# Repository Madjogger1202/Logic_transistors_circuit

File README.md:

# Logic_transistors_circuit

**Демонстрационная плата логических вентилей OR, AND и NOT на дискретных транзисторах с питанием от USB.**

Наглядная плата, на которой базовые логические вентили — **OR**, **AND** и **NOT** — собраны на дискретных транзисторах. Питание от USB, входы и выходы выведены на контактные площадки, оформление с обозначениями вентилей прямо на шелкографии. Завершающая плата из серии простых схемотехнических узлов.

## Обзор

- **Название проекта:** Logic_transistors_circuit
- **Назначение:** наглядная реализация логических вентилей на транзисторах
- **Вентили:** OR, AND, NOT
- **Элементная база:** дискретные транзисторы
- **Питание:** USB

## Ключевые особенности

- **Три базовых вентиля** — OR, AND и NOT, каждый собран на дискретных транзисторах
- **Транзисторная логика без микросхем** — наглядно показывает, как из транзисторов строится цифровая логика
- **Питание от USB** — простое подключение, не нужен отдельный источник
- **Выведенные контакты** — входы и выходы каждого вентиля доступны для подачи сигналов и индикации
- **Аккуратное оформление** — обозначения вентилей на шелкографии, плата как наглядное/учебное пособие

## Что на плате

| Блок | Назначение |
|---|---|
| Вентиль OR | Логическое «ИЛИ» на транзисторах |
| Вентиль AND | Логическое «И» на транзисторах |
| Вентиль NOT | Инвертор на транзисторе |
| Контактные площадки | Входы/выходы вентилей для сигналов и индикации |
| Питание | USB |

## Применение

- Наглядное изучение транзисторной логики
- Демонстрация принципов работы базовых вентилей
- Учебное пособие по схемотехнике цифровых узлов
- Эффектная «инженерная» плата для коллекции

## Среда разработки

- **Схема и плата:** KiCad

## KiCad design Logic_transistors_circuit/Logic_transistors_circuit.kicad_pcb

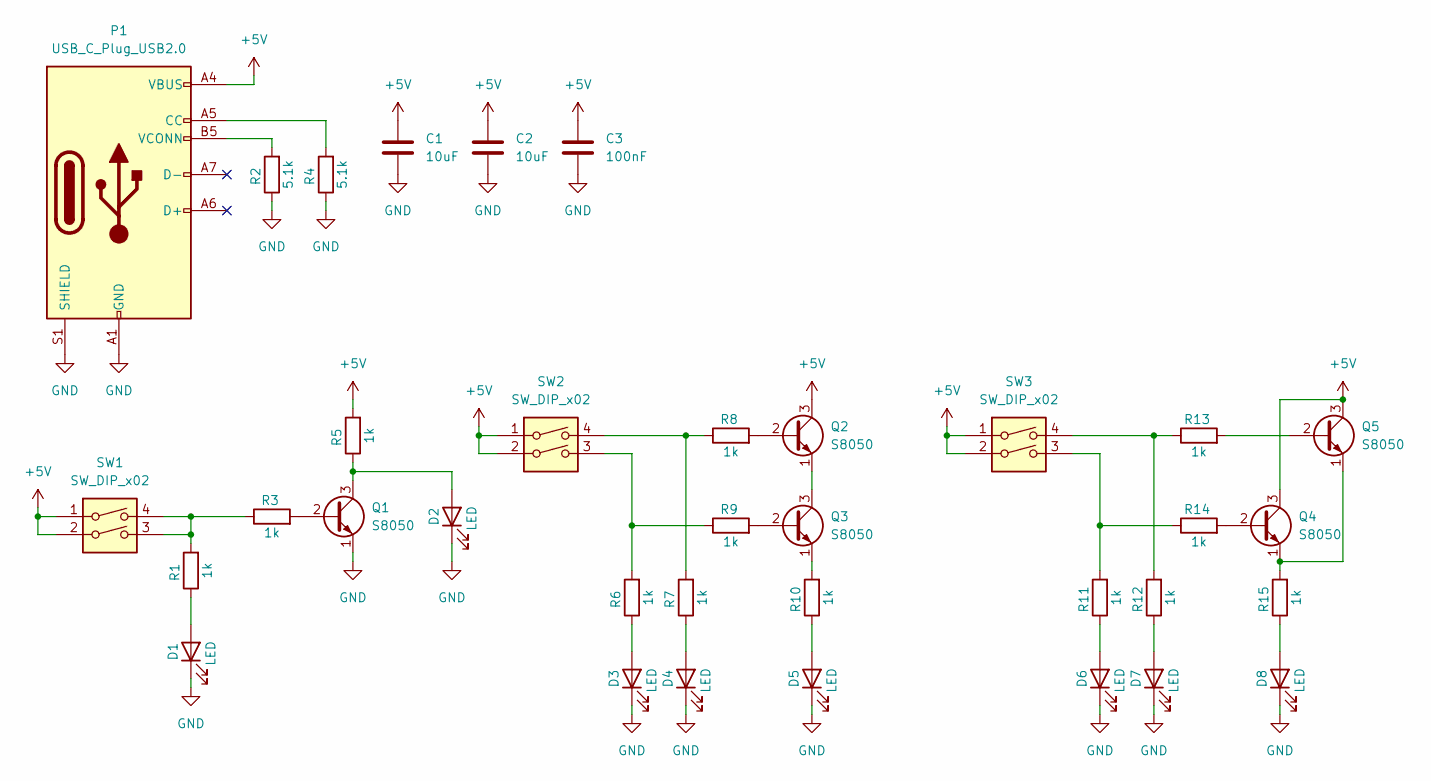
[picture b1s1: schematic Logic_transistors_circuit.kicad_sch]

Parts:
C1, C2: 10uF; C_0805_2012Metric
C3: 100nF; C_0805_2012Metric
D1, D2, D3, D4, D5, D6, D7, D8: LED; LED_0603_1608Metric
P1: USB_C_Plug_USB2.0; USB_C_Receptacle_JAE_DX07S016JA1R1500
Q1, Q2, Q3, Q4, Q5: S8050; SOT-23
R1, R3, R5, R6, R7, R8, R9, R10, R11, R12, R13, R14, R15: 1k; R_0603_1608Metric
R2, R4: 5.1k; R_0603_1608Metric
SW1, SW2, SW3: SW_DIP_x02; SW_DIP_SPSTx02_Slide_9.78x7.26mm_W7.62mm_P2.54mm

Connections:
+5V: C1.1, C2.1, C3.1, P1.A4 (VBUS), P1.A9 (VBUS), P1.B4 (VBUS), P1.B9 (VBUS), Q2.3 (C), Q4.3 (C), Q5.3 (C), R5.2, SW1.1, SW1.2, SW2.1, SW2.2, SW3.1, SW3.2
GND: C1.2, C2.2, C3.2, D1.1 (K), D2.1 (K), D3.1 (K), D4.1 (K), D5.1 (K), D6.1 (K), D7.1 (K), D8.1 (K), P1.A1 (GND), P1.A12 (GND), P1.B1 (GND), P1.B12 (GND), P1.S1 (SHIELD), Q1.1 (E), R2.1, R4.1
unnamed: D1.2 (A), R1.1
unnamed: D2.2 (A), Q1.3 (C), R5.1
unnamed: D3.2 (A), R6.1
unnamed: D4.2 (A), R7.1
unnamed: D5.2 (A), R10.1
unnamed: D6.2 (A), R11.1
unnamed: D7.2 (A), R12.1
unnamed: D8.2 (A), R15.1
unnamed: P1.A5 (CC), R4.2
unnamed: P1.B5 (VCONN), R2.2
unnamed: Q1.2 (B), R3.2
unnamed: Q2.2 (B), R8.2
unnamed: Q2.1 (E), Q3.3 (C)
unnamed: Q3.2 (B), R9.2
unnamed: Q3.1 (E), R10.2
unnamed: Q4.2 (B), R14.2
unnamed: Q4.1 (E), Q5.1 (E), R15.2
unnamed: Q5.2 (B), R13.2
unnamed: R1.2, R3.1, SW1.3, SW1.4
unnamed: R6.2, R9.1, SW2.3
unnamed: R7.2, R8.1, SW2.4
unnamed: R11.2, R14.1, SW3.3
unnamed: R12.2, R13.1, SW3.4

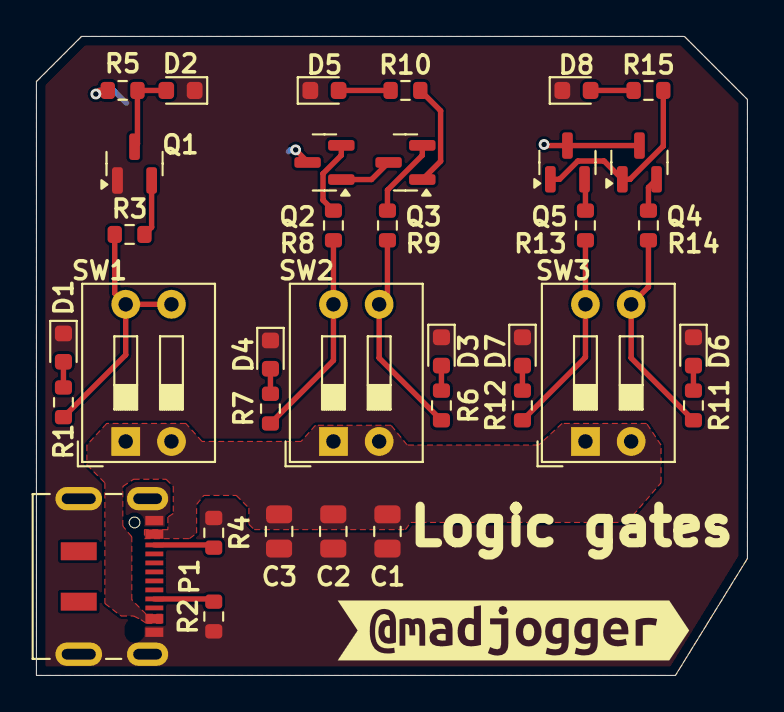
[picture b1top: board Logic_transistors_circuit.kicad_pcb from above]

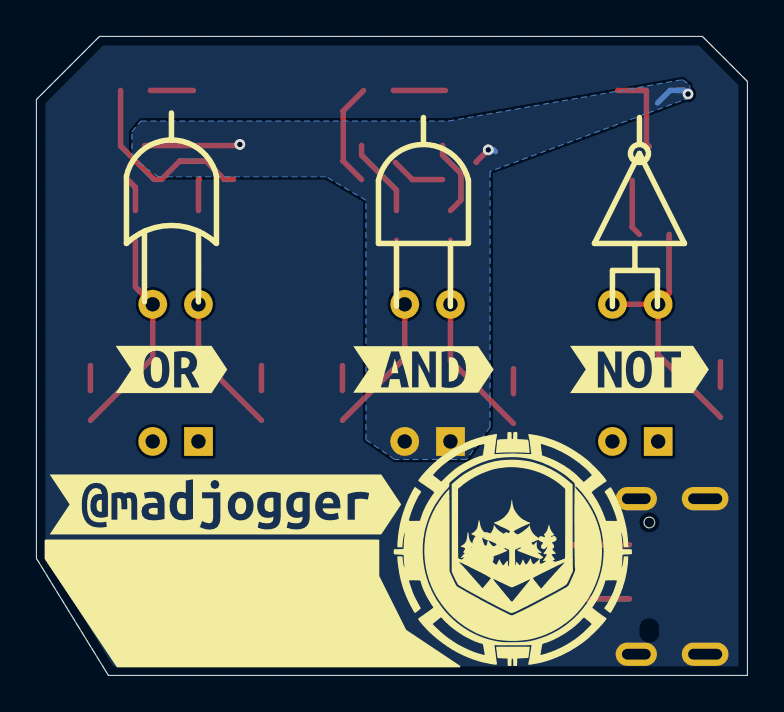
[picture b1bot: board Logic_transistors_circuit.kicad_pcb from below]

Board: 2 copper layers, 39.5 x 35.5 mm, 40 parts (4 on the bottom side), 25 nets.

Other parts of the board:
kibuzzard-678D16F5: G***; kibuzzard-678D16F5
kibuzzard-678D163D: G***; kibuzzard-678D163D
kibuzzard-678D167B: G***; kibuzzard-678D167B
kibuzzard-678D0313, kibuzzard-678D0313#2: G***; kibuzzard-678D0313

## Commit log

2025-01-19 rev0
